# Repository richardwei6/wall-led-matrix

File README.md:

# wall-led-matrix
 HOPE KiCAD Wireless Wall LED matrix

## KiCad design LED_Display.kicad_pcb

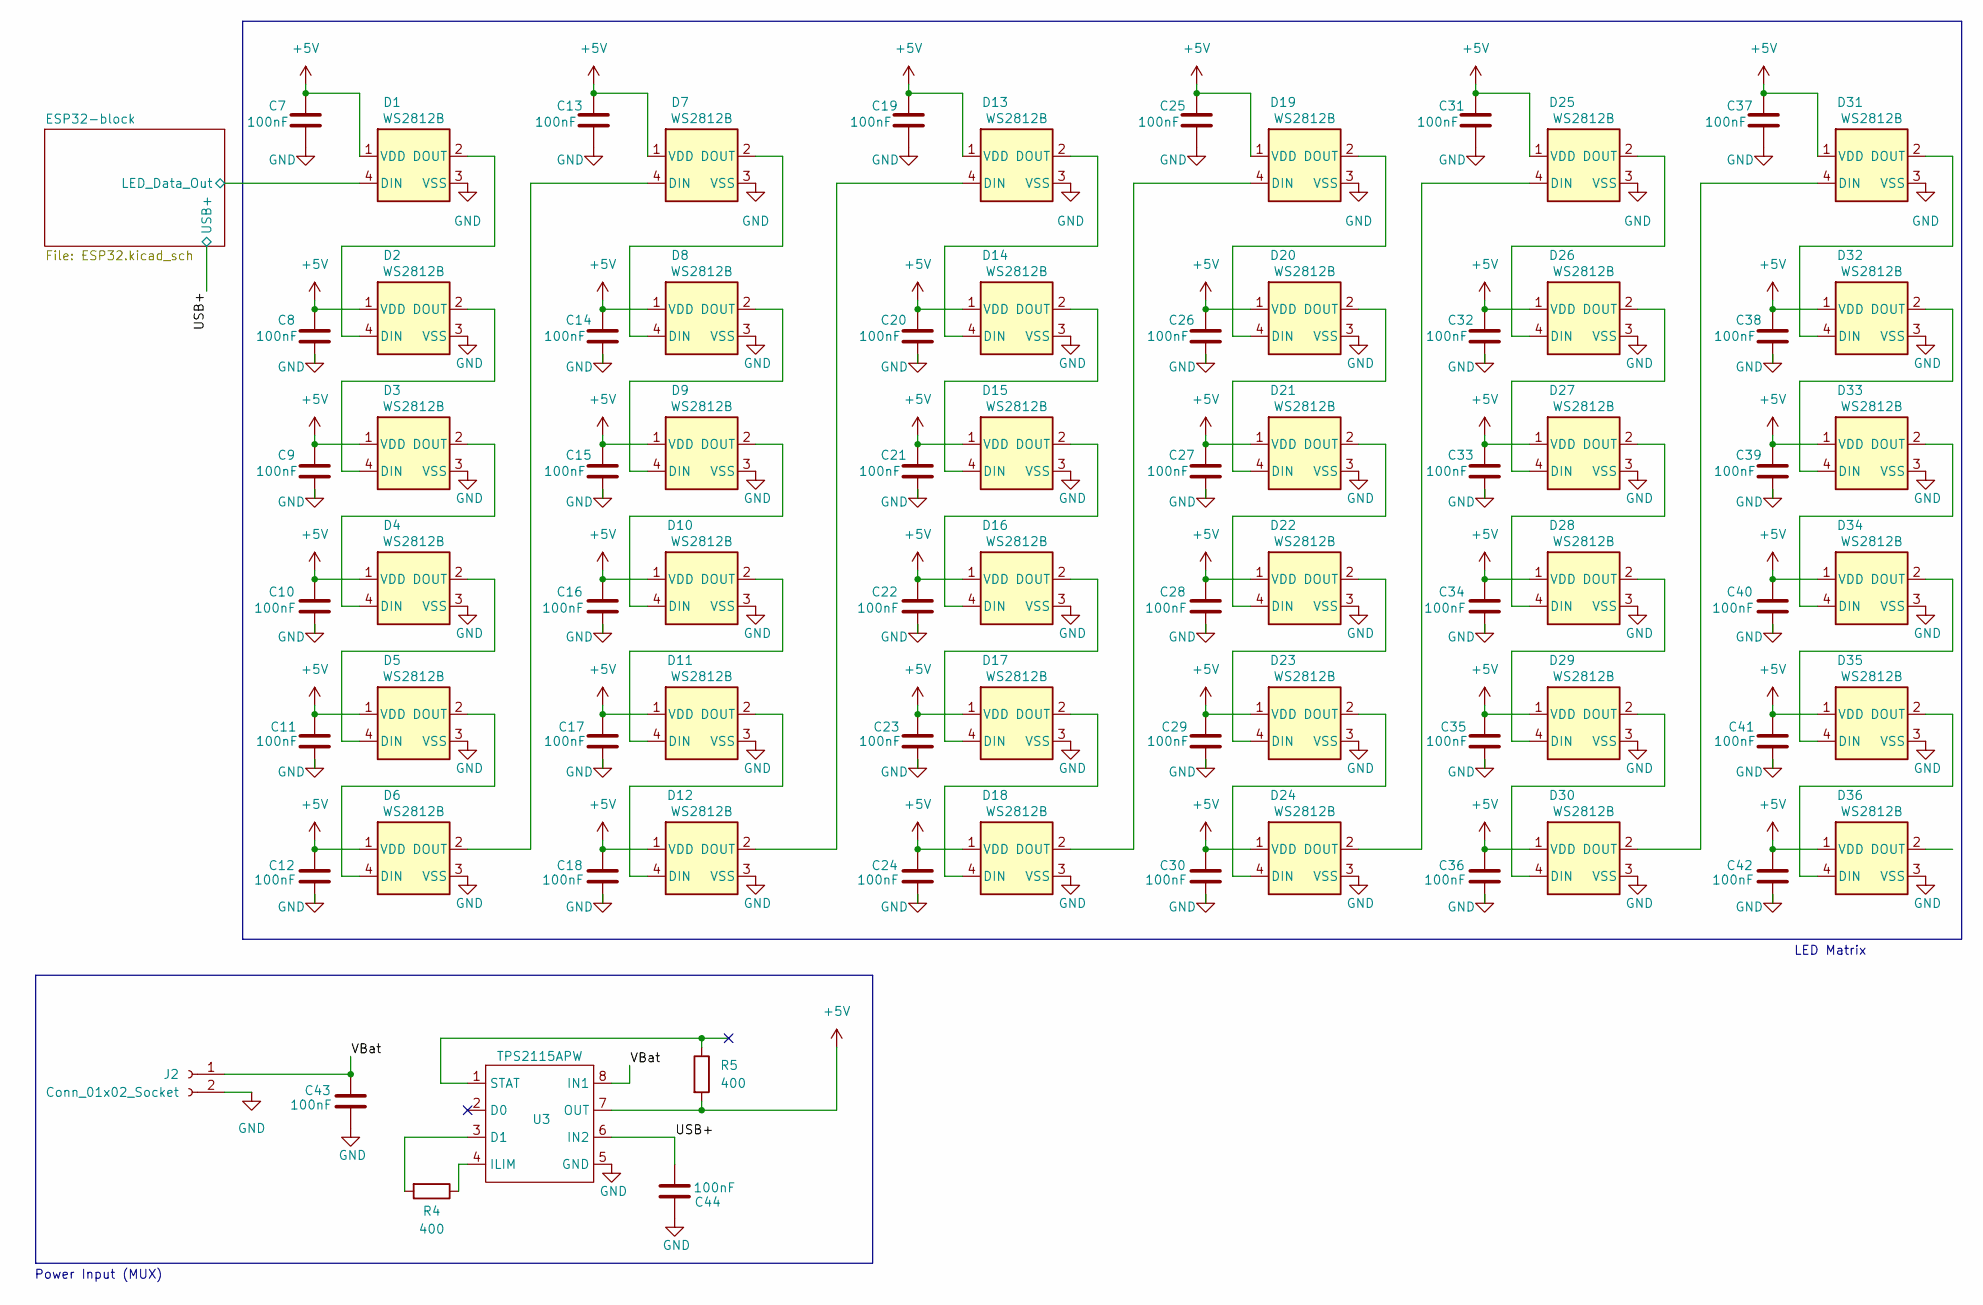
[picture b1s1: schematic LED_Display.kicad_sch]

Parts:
C7, C8, C9, C10, C11, C12, C13, C14, C15, C16, C17, C18, C19, C20, C21, C22, C23, C24, C25, C26, C27, C28, C29, C30, C31, C32, C33, C34, C35, C36, C37, C38, C39, C40, C41, C42, C43, C44: 100nF; C_0603_1608Metric
D1, D2, D3, D4, D5, D6, D7, D8, D9, D10, D11, D12, D13, D14, D15, D16, D17, D18, D19, D20, D21, D22, D23, D24, D25, D26, D27, D28, D29, D30, D31, D32, D33, D34, D35, D36: WS2812B; LED_WS2812B_PLCC4_5.0x5.0mm_P3.2mm
J2: Conn_01x02_Socket; PinHeader_1x02_P1.00mm_Horizontal
R4, R5: 400; R_1206_3216Metric
U3: TPS2115APW; SON65P300X300X100-9N

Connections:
+5V: C7.1, C8.1, C9.1, C10.1, C11.1, C12.1, C13.1, C14.1, C15.1, C16.1, C17.1, C18.1, C19.1, C20.1, C21.1, C22.1, C23.1, C24.1, C25.1, C26.1, C27.1, C28.1, C29.1, C30.1, C31.1, C32.1, C33.1, C34.1, C35.1, C36.1, C37.1, C38.1, C39.1, C40.1, C41.1, C42.1, D1.1 (VDD), D2.1 (VDD), D3.1 (VDD), D4.1 (VDD), D5.1 (VDD), D6.1 (VDD), D7.1 (VDD), D8.1 (VDD), D9.1 (VDD), D10.1 (VDD), D11.1 (VDD), D12.1 (VDD), D13.1 (VDD), D14.1 (VDD), D15.1 (VDD), D16.1 (VDD), D17.1 (VDD), D18.1 (VDD), D19.1 (VDD), D20.1 (VDD), D21.1 (VDD), D22.1 (VDD), D23.1 (VDD), D24.1 (VDD), D25.1 (VDD), D26.1 (VDD), D27.1 (VDD), D28.1 (VDD), D29.1 (VDD), D30.1 (VDD), D31.1 (VDD), D32.1 (VDD), D33.1 (VDD), D34.1 (VDD), D35.1 (VDD), D36.1 (VDD), R5.2, U3.7 (OUT); also elsewhere on the board
/ESP32-block/LED_Data_Out: D1.4 (DIN); also elsewhere on the board
/USB+: C44.2, U3.6 (IN2); also elsewhere on the board
/VBat: C43.1, J2.1, U3.8 (IN1)
GND: C7.2, C8.2, C9.2, C10.2, C11.2, C12.2, C13.2, C14.2, C15.2, C16.2, C17.2, C18.2, C19.2, C20.2, C21.2, C22.2, C23.2, C24.2, C25.2, C26.2, C27.2, C28.2, C29.2, C30.2, C31.2, C32.2, C33.2, C34.2, C35.2, C36.2, C37.2, C38.2, C39.2, C40.2, C41.2, C42.2, C43.2, C44.1, D1.3 (VSS), D2.3 (VSS), D3.3 (VSS), D4.3 (VSS), D5.3 (VSS), D6.3 (VSS), D7.3 (VSS), D8.3 (VSS), D9.3 (VSS), D10.3 (VSS), D11.3 (VSS), D12.3 (VSS), D13.3 (VSS), D14.3 (VSS), D15.3 (VSS), D16.3 (VSS), D17.3 (VSS), D18.3 (VSS), D19.3 (VSS), D20.3 (VSS), D21.3 (VSS), D22.3 (VSS), D23.3 (VSS), D24.3 (VSS), D25.3 (VSS), D26.3 (VSS), D27.3 (VSS), D28.3 (VSS), D29.3 (VSS), D30.3 (VSS), D31.3 (VSS), D32.3 (VSS), D33.3 (VSS), D34.3 (VSS), D35.3 (VSS), D36.3 (VSS), J2.2, U3.5 (GND); also elsewhere on the board
unnamed: D1.2 (DOUT), D2.4 (DIN)
unnamed: D2.2 (DOUT), D3.4 (DIN)
unnamed: D3.2 (DOUT), D4.4 (DIN)
unnamed: D4.2 (DOUT), D5.4 (DIN)
unnamed: D5.2 (DOUT), D6.4 (DIN)
unnamed: D6.2 (DOUT), D7.4 (DIN)
unnamed: D7.2 (DOUT), D8.4 (DIN)
unnamed: D8.2 (DOUT), D9.4 (DIN)
unnamed: D9.2 (DOUT), D10.4 (DIN)
unnamed: D10.2 (DOUT), D11.4 (DIN)
unnamed: D11.2 (DOUT), D12.4 (DIN)
unnamed: D12.2 (DOUT), D13.4 (DIN)
unnamed: D13.2 (DOUT), D14.4 (DIN)
unnamed: D14.2 (DOUT), D15.4 (DIN)
unnamed: D15.2 (DOUT), D16.4 (DIN)
unnamed: D16.2 (DOUT), D17.4 (DIN)
unnamed: D17.2 (DOUT), D18.4 (DIN)
unnamed: D18.2 (DOUT), D19.4 (DIN)
unnamed: D19.2 (DOUT), D20.4 (DIN)
unnamed: D20.2 (DOUT), D21.4 (DIN)
unnamed: D21.2 (DOUT), D22.4 (DIN)
unnamed: D22.2 (DOUT), D23.4 (DIN)
unnamed: D23.2 (DOUT), D24.4 (DIN)
unnamed: D24.2 (DOUT), D25.4 (DIN)
unnamed: D25.2 (DOUT), D26.4 (DIN)
unnamed: D26.2 (DOUT), D27.4 (DIN)
unnamed: D27.2 (DOUT), D28.4 (DIN)
unnamed: D28.2 (DOUT), D29.4 (DIN)
unnamed: D29.2 (DOUT), D30.4 (DIN)
unnamed: D30.2 (DOUT), D31.4 (DIN)
unnamed: D31.2 (DOUT), D32.4 (DIN)
unnamed: D32.2 (DOUT), D33.4 (DIN)
unnamed: D33.2 (DOUT), D34.4 (DIN)
unnamed: D34.2 (DOUT), D35.4 (DIN)
unnamed: D35.2 (DOUT), D36.4 (DIN)
unnamed: R4.2, U3.3 (D1)
unnamed: R4.1, U3.4 (ILIM)

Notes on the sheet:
LED Matrix
Power Input (MUX)

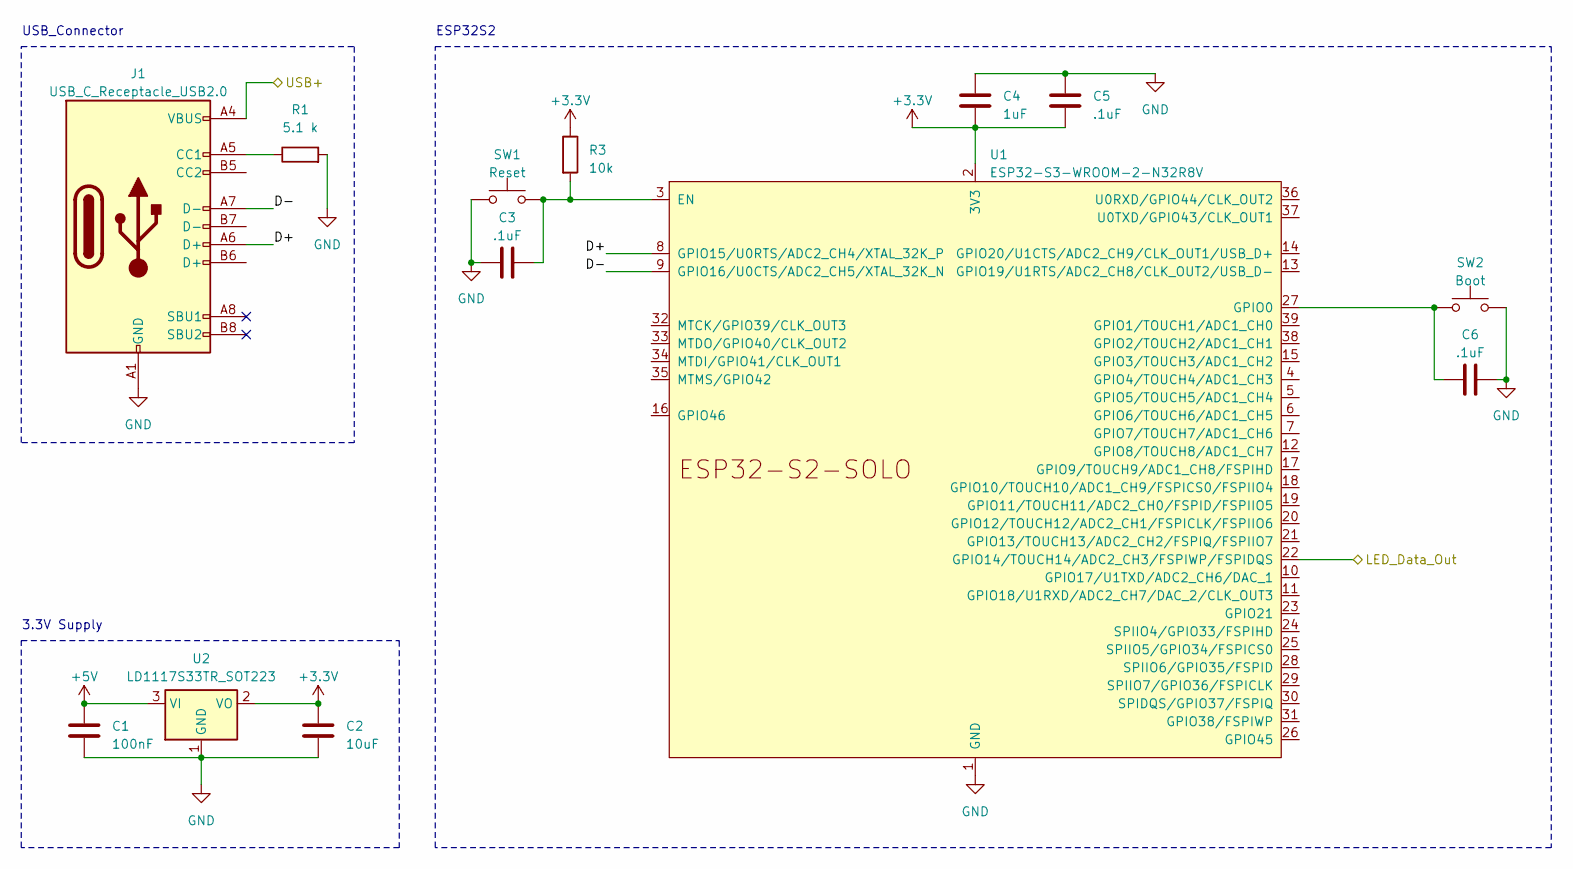
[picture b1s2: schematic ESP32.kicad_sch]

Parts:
C1: 100nF; C_0603_1608Metric
C2: 10uF; C_0603_1608Metric
C3, C5, C6: .1uF; C_0603_1608Metric
C4: 1uF; C_0603_1608Metric
J1: USB_C_Receptacle_USB2.0; CUI_UJ31-CH-G2-SMT-TR
R1: 5.1 k; R_0603_1608Metric
R3: 10k; R_0603_1608Metric
SW1: Reset; SOIC_FS-1000P_OMR
SW2: Boot; SOIC_FS-1000P_OMR
U1: ESP32-S3-WROOM-2-N32R8V; ESP32-S3-WROOM-2
U2: LD1117S33TR_SOT223; SOT-223-3_TabPin2

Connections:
+3.3V: C2.1, C4.2, C5.2, R3.1, U1.2 (3V3), U2.2 (VO)
+5V: C1.1, U2.3 (VI); also elsewhere on the board
/ESP32-block/D+: J1.A6 (D+), U1.8 (GPIO15/U0RTS/ADC2_CH4/XTAL_32K_P)
/ESP32-block/D-: J1.A7 (D-), U1.9 (GPIO16/U0CTS/ADC2_CH5/XTAL_32K_N)
/ESP32-block/LED_Data_Out: U1.22 (GPIO14/TOUCH14/ADC2_CH3/FSPIWP/FSPIDQS); also elsewhere on the board
/USB+: J1.A4 (VBUS), J1.A9 (VBUS), J1.B4 (VBUS), J1.B9 (VBUS); also elsewhere on the board
GND: C1.2, C2.2, C3.1, C4.1, C5.1, C6.2, J1.A1 (GND), J1.A12 (GND), J1.B1 (GND), J1.B12 (GND), R1.2, SW1.1, SW2.2, U1.1 (GND), U1.40 (GND), U1.41 (GND), U2.1 (GND); also elsewhere on the board
unnamed: J1.A5 (CC1), R1.1
unnamed: C3.2, R3.2, SW1.2, U1.3 (EN)
unnamed: C6.1, SW2.1, U1.27 (GPIO0)

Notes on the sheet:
3.3V Supply
ESP32S2
USB_Connector

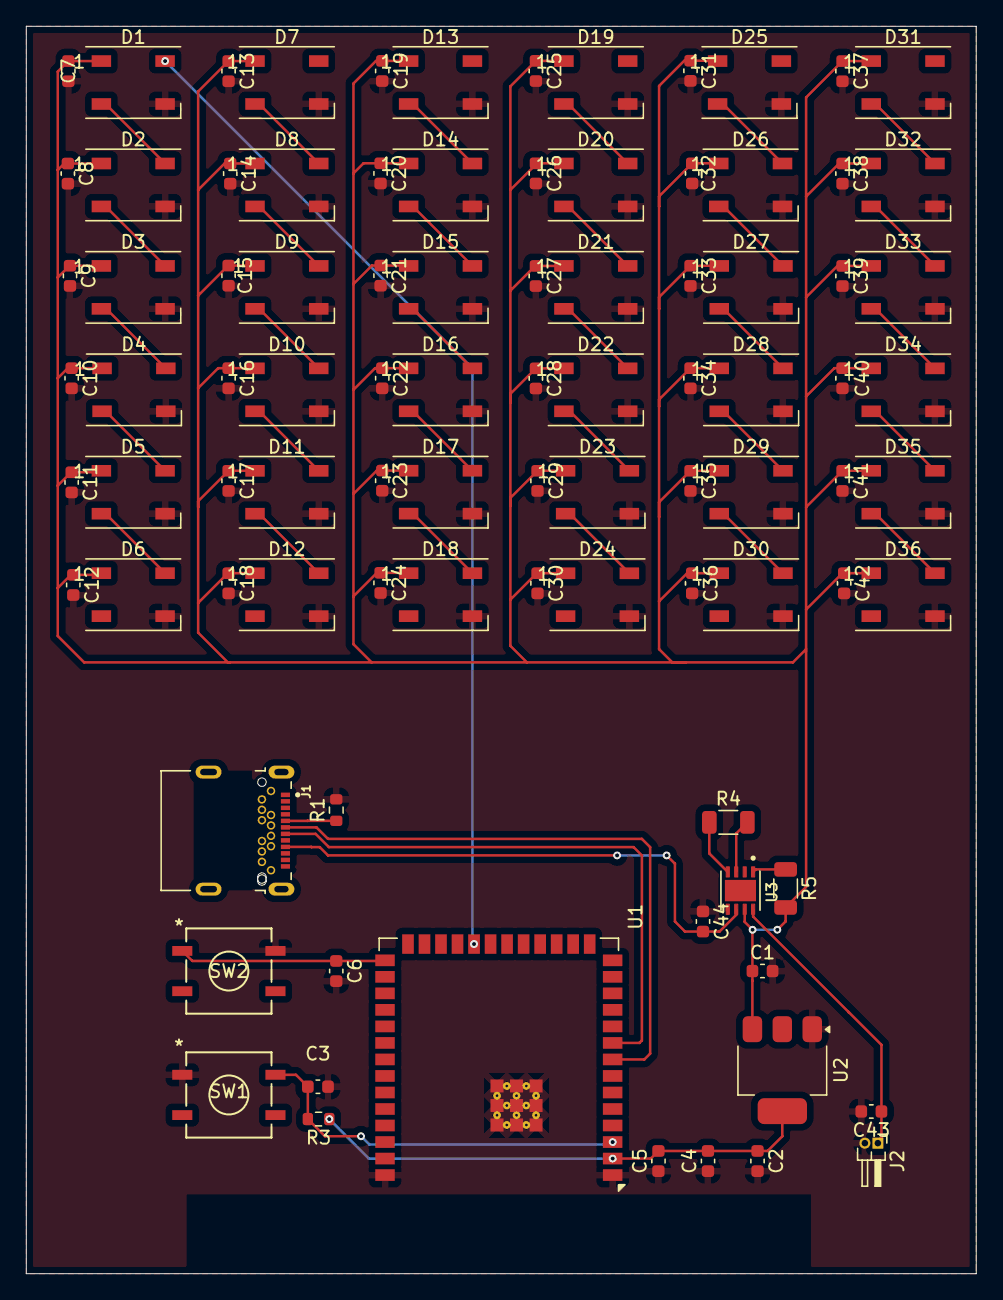
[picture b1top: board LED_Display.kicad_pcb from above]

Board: 2 copper layers, 73.0 x 95.9 mm, 91 parts (0 on the bottom side), 48 nets.

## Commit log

2024-10-30 Upload project
2024-12-06 New file for LED firmware.
2024-12-06 Basic FastLED control.
